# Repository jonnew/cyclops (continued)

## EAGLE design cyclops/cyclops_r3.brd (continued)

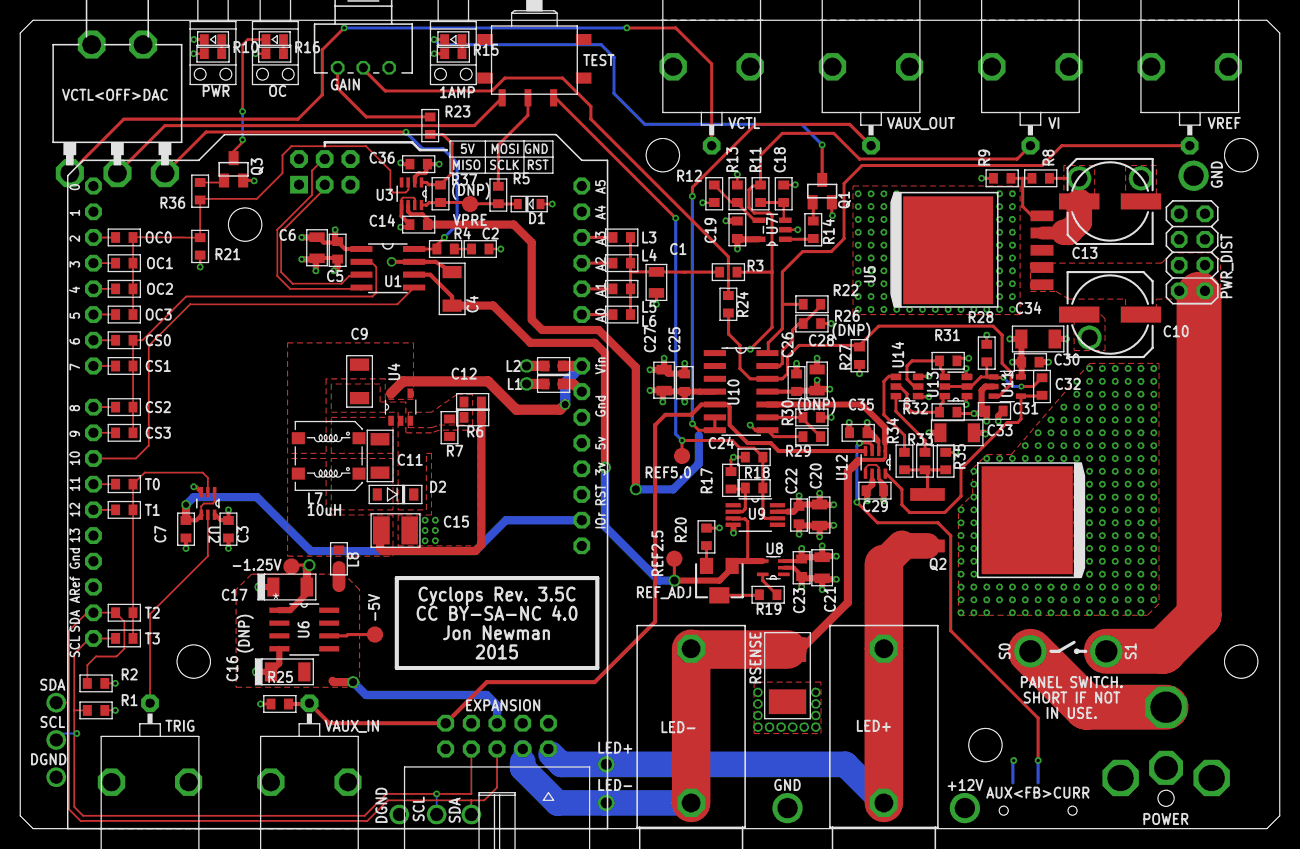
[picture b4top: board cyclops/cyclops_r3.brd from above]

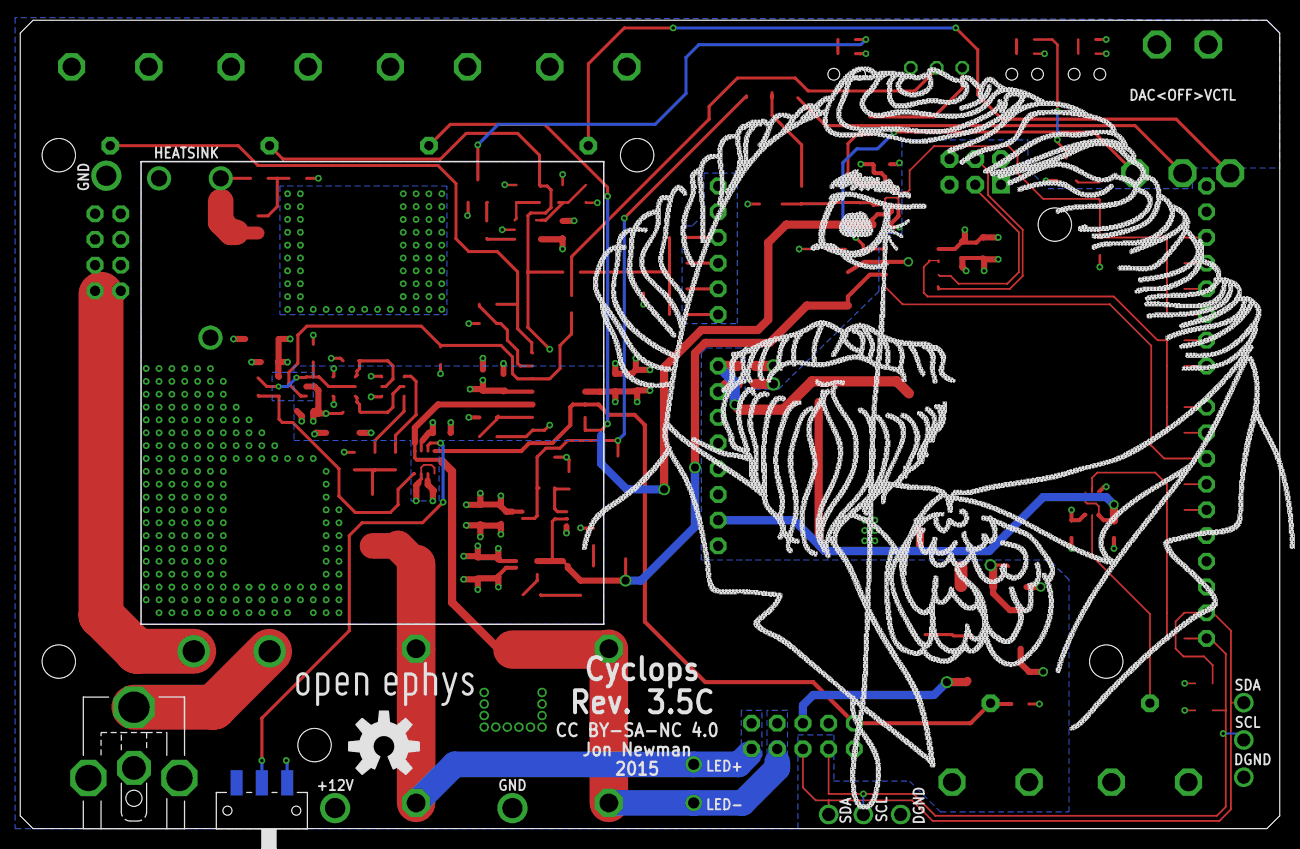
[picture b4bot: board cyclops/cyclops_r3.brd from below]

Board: 4 copper layers, 124.5 x 79.9 mm, 144 parts (6 on the bottom side), 80 nets.

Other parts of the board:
U$30: OPEN_EPHYS_LOGO
U$56: CYCLOPS_LOGO
U$60: OSHW-LOGO-L

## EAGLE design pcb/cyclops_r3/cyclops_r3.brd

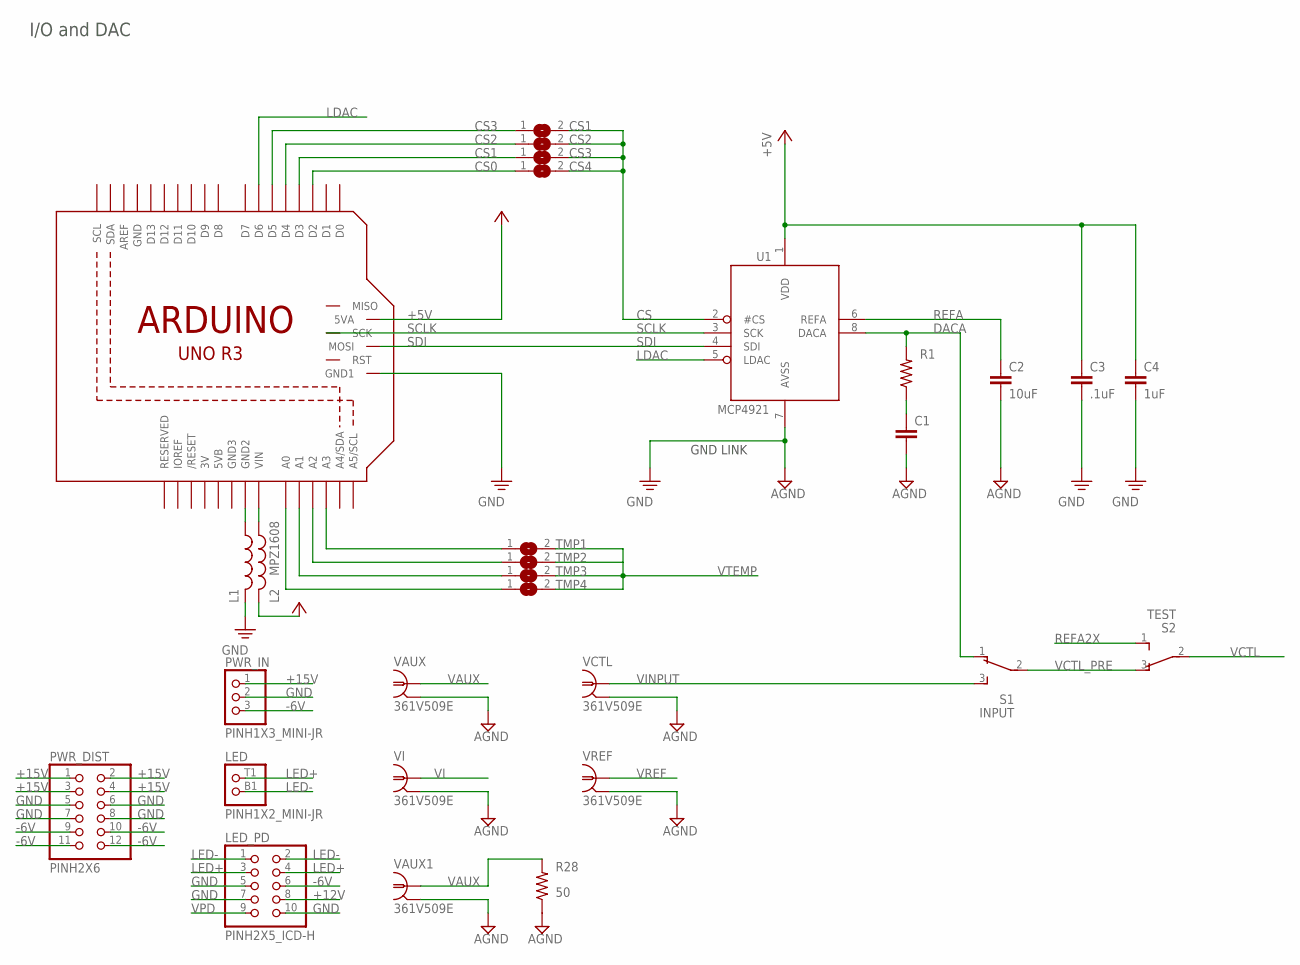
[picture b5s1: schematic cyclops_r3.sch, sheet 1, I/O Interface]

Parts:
ARDUNIO: ARDUINO_R3_ICSP_PINS; ARUDINOR3_PINS
C1: C_0603; 0603
C2: 10uF; 0805
C3: .1uF; 0603
C4: 1uF; 0805
CS1, CS2, CS3, CS4: SJ
L1, L2: MPZ1608; 0805
LED: PINH1X2_MINI-JR; MINI-JR-2X1
LED_PD: PINH2X5_ICD-H; 2X05-IDC
PWR_DIST: PINH2X6; 2X06-BIG
PWR_IN: PINH1X3_MINI-JR; MINI-JR-1X3
R1: R_0603; 0603
R28: 50; 0603
S1: INPUT; JS102011SAQN
S2: TEST; CFPA
TMP1, TMP2, TMP3, TMP4: SJ
U1: MCP4921; SO08
VAUX, VAUX1: 361V509E
VCTL: 361V509E
VI: 361V509E
VREF: 361V509E

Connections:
+5V: ARDUNIO.5VA, C3.1, C4.1, U1.1 (VDD)
+12V: L2.2, LED_PD.8; also elsewhere on the board
+15V: PWR_DIST.1, PWR_DIST.2, PWR_DIST.3, PWR_DIST.4, PWR_IN.1; also elsewhere on the board
-6V: LED_PD.6, PWR_DIST.9, PWR_DIST.10, PWR_DIST.11, PWR_DIST.12, PWR_IN.3; also elsewhere on the board
AGND: R28.1
CS: CS1.2, CS2.2, CS3.2, CS4.2, U1.2 (#CS)
CS0: ARDUNIO.D2, CS4.1
CS1: ARDUNIO.D3, CS3.1
CS2: ARDUNIO.D4, CS2.1
CS3: ARDUNIO.D5, CS1.1
CS4: ARDUNIO.A0, TMP4.1
CS5: ARDUNIO.A1, TMP3.1
CS6: ARDUNIO.A3, TMP1.1
CS8: ARDUNIO.A2, TMP2.1
DACA: R1.2, S1.1, U1.8 (DACA)
GND: ARDUNIO.GND1, C1.2, C2.2, C3.2, C4.2, L1.2, LED_PD.5, LED_PD.7, LED_PD.10, PWR_DIST.5, PWR_DIST.6, PWR_DIST.7, PWR_DIST.8, PWR_IN.2, U1.7 (AVSS), VAUX.2, VAUX.3 (2), VAUX1.2, VAUX1.3 (2), VCTL.2, VCTL.3 (2), VI.2, VI.3 (2), VREF.2, VREF.3 (2); also elsewhere on the board
LDAC: ARDUNIO.D6, U1.5 (LDAC)
LED+: LED.T1 (1), LED_PD.3, LED_PD.4; also elsewhere on the board
LED-: LED.B1 (2), LED_PD.1, LED_PD.2; also elsewhere on the board
unnamed: C1.1, R1.1
unnamed: ARDUNIO.GND2, L1.1
unnamed: ARDUNIO.VIN, L2.1
REFA: C2.1, U1.6 (REFA); also elsewhere on the board
REFA2X: S2.1 (3); also elsewhere on the board
SCLK: ARDUNIO.SCK, U1.3 (SCK)
SDI: ARDUNIO.MOSI, U1.4 (SDI)
VAUX: R28.2, VAUX.1, VAUX1.1; also elsewhere on the board
VCTL: S2.2; also elsewhere on the board
VCTL_PRE: S1.2, S2.3 (1)
VI: VI.1; also elsewhere on the board
VINPUT: S1.3, VCTL.1
VPD: LED_PD.9; also elsewhere on the board
VREF: VREF.1; also elsewhere on the board
VTEMP: TMP1.2, TMP2.2, TMP3.2, TMP4.2; also elsewhere on the board

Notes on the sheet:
GND LINK
I/O and DAC

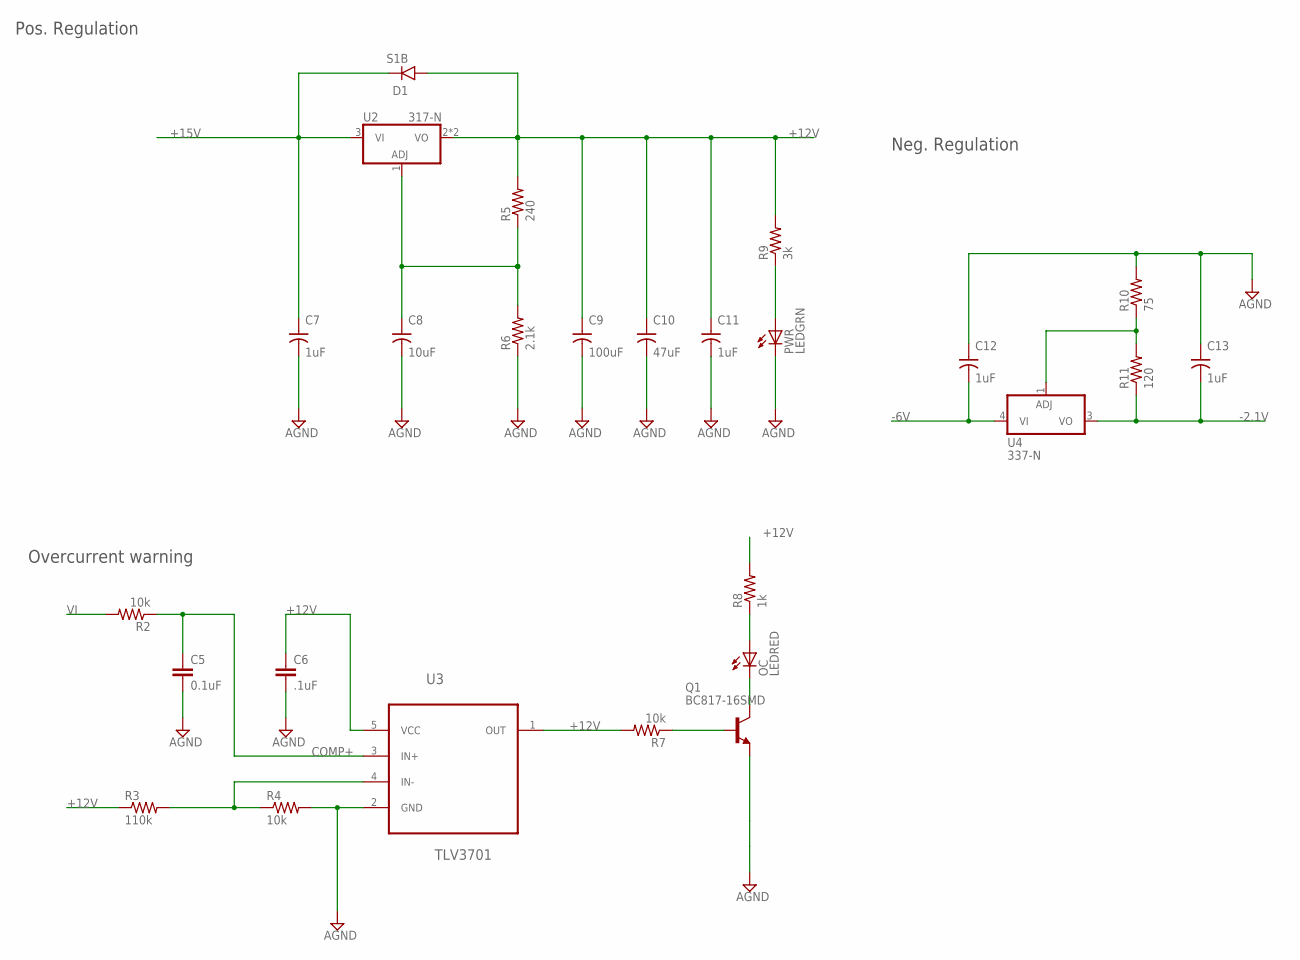
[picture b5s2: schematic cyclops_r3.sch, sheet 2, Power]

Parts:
C5: 0.1uF; 0603
C6: .1uF; 0603
C7, C11, C12, C13: 1uF; 1206-POL
C8: 10uF; 1206-POL
C9: 100uF; 153CLV-0807
C10: 47uF; 153CLV-0807
D1: S1B; SMA-DO214AC
OC: LEDRED; LED-0603
PWR: LEDGRN; LED-0603
Q1: BC817-16SMD; SOT23-BEC
R2, R4, R7: 10k; 0603
R3: 110k; 0603
R5: 240; 0603
R6: 2.1k; 0603
R8: 1k; 0603
R9: 3k; 0603
R10: 75; 0603
R11: 120; 0603
U2: 317-N; TO-263
U3: TLV3701; SOT95P280X145-5N
U4: 337-N; SOT223

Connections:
+12V: C6.1, C9.+, C10.+, C11.+, D1.A, R3.1, R5.2, R8.2, R9.2, U2.2 (VO), U2.4 (VO), U3.5 (VCC); also elsewhere on the board
+15V: C7.+, D1.C, U2.3 (VI); also elsewhere on the board
-2.1V: C13.-, R11.1, U4.3 (VO); also elsewhere on the board
-6V: C12.-, U4.4 (VI); also elsewhere on the board
COMP+: C5.1, R2.1, U3.3 (IN+)
GND: C5.2, C6.2, C7.-, C8.-, C9.-, C10.-, C11.-, C12.+, C13.+, PWR.C, Q1.E, R4.2, R6.1, R10.2, U3.2 (GND); also elsewhere on the board
unnamed: OC.A, R8.1
unnamed: PWR.A, R9.1
unnamed: R3.2, R4.1, U3.4 (IN-)
unnamed: OC.C, Q1.C
unnamed: R10.1, R11.2, U4.1 (ADJ)
unnamed: R7.2, U3.1 (OUT)
unnamed: Q1.B, R7.1
unnamed: C8.+, R5.1, R6.2, U2.1 (ADJ)
VI: R2.2; also elsewhere on the board

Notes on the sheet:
Pos. Regulation
Overcurrent warning
Neg. Regulation

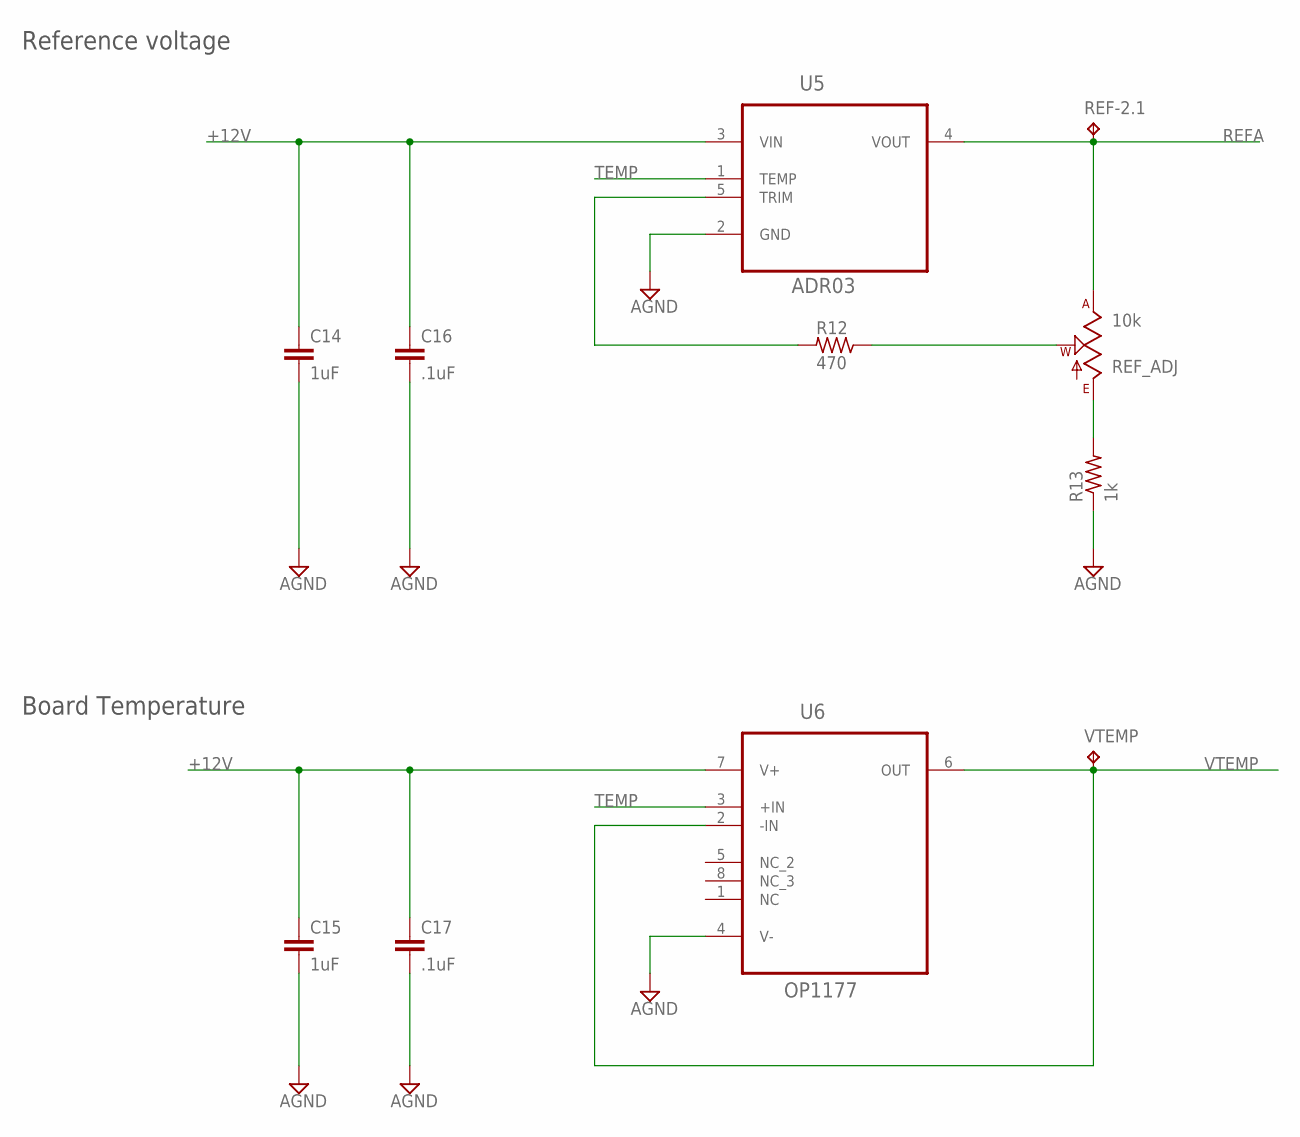
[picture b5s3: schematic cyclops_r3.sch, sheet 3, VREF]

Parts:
C14, C15: 1uF; 0805
C16, C17: .1uF; 0603
R12: 470; 0603
R13: 1k; 0603
REF-2.1: TPTP08R; TP08R
REF_ADJ: 10k; SM-42/43W
U5: ADR03; SOT65P210X110-5N
U6: OP1177; SOP65P490X110-8N
VTEMP: TPTP08R; TP08R

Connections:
+12V: C14.1, C15.1, C16.1, C17.1, U5.3 (VIN), U6.7 (V+); also elsewhere on the board
GND: C14.2, C15.2, C16.2, C17.2, R13.1, U5.2 (GND), U6.4 (V-); also elsewhere on the board
unnamed: R13.2, REF_ADJ.3 (E)
unnamed: R12.2, U5.5 (TRIM)
unnamed: R12.1, REF_ADJ.2 (W)
REFA: REF-2.1.TP, REF_ADJ.1 (A), U5.4 (VOUT); also elsewhere on the board
TEMP: U5.1 (TEMP), U6.3 (+IN)
VTEMP: U6.2 (-IN), U6.6 (OUT), VTEMP.TP; also elsewhere on the board

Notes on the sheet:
Reference voltage
Board Temperature

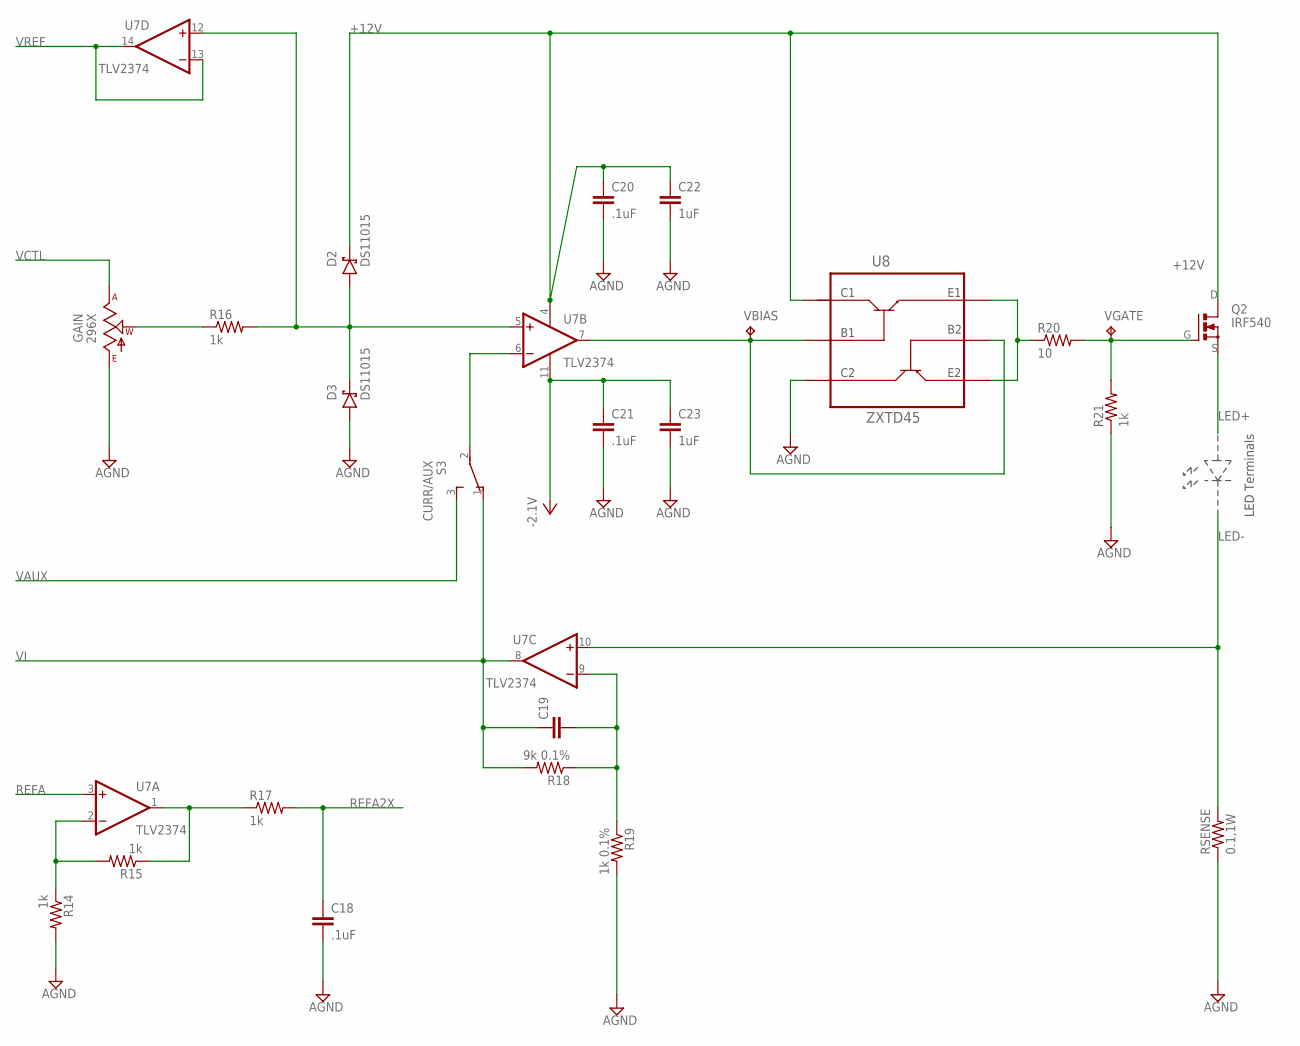
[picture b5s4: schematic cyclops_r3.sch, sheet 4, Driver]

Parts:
C18, C20, C21: .1uF; 0603
C19: C_0603; 0603
C22, C23: 1uF; 0805
D2, D3: DS11015; SOD123
GAIN: 296X; 296X-POT
Q2: IRF540; TO-262_01
R14, R15, R16, R17, R21: 1k; 0603
R18: 9k 0.1%; 0603
R19: 1k 0.1%; 0603
R20: 10; 0603
RSENSE: 0.1,1W; 2512W
S3: CURR/AUX; JS102011SAQN
U7: TLV2374; SO14
U8: ZXTD45; SOT23-6
VBIAS: TPTP08R; TP08R
VGATE: TPTP08R; TP08R

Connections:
+12V: C20.1, C22.1, D2.C, Q2.D, U7.4 (V+), U8.1 (C1); also elsewhere on the board
-2.1V: C21.1, C23.1, U7.11 (V-); also elsewhere on the board
GND: C18.2, C20.2, C21.2, C22.2, C23.2, D3.A, GAIN.E, R14.2, R19.2, R21.1, RSENSE.1, U8.3 (C2); also elsewhere on the board
LED+: Q2.S; also elsewhere on the board
LED-: RSENSE.2, U7.10 (+IN); also elsewhere on the board
unnamed: U7.7 (OUT), U8.2 (B1), U8.5 (B2), VBIAS.TP
unnamed: GAIN.W, R16.1
unnamed: R14.1, R15.2, U7.2 (-IN)
unnamed: R20.1, U8.4 (E2), U8.6 (E1)
unnamed: Q2.G, R20.2, R21.2, VGATE.TP
unnamed: C19.2, R18.1, R19.1, U7.9 (-IN)
REFA: U7.3 (+IN); also elsewhere on the board
REFA2X: C18.1, R17.2; also elsewhere on the board
VAUX: S3.3; also elsewhere on the board
VCTL: GAIN.A; also elsewhere on the board
VFB: S3.2, U7.6 (-IN)
VI: C19.1, R18.2, S3.1, U7.8 (OUT); also elsewhere on the board
VREF: U7.13 (-IN), U7.14 (OUT); also elsewhere on the board
VREFA2X: R15.1, R17.1, U7.1 (OUT)
_VREF: D2.A, D3.C, R16.2, U7.5 (+IN), U7.12 (+IN)

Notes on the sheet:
LED Terminals

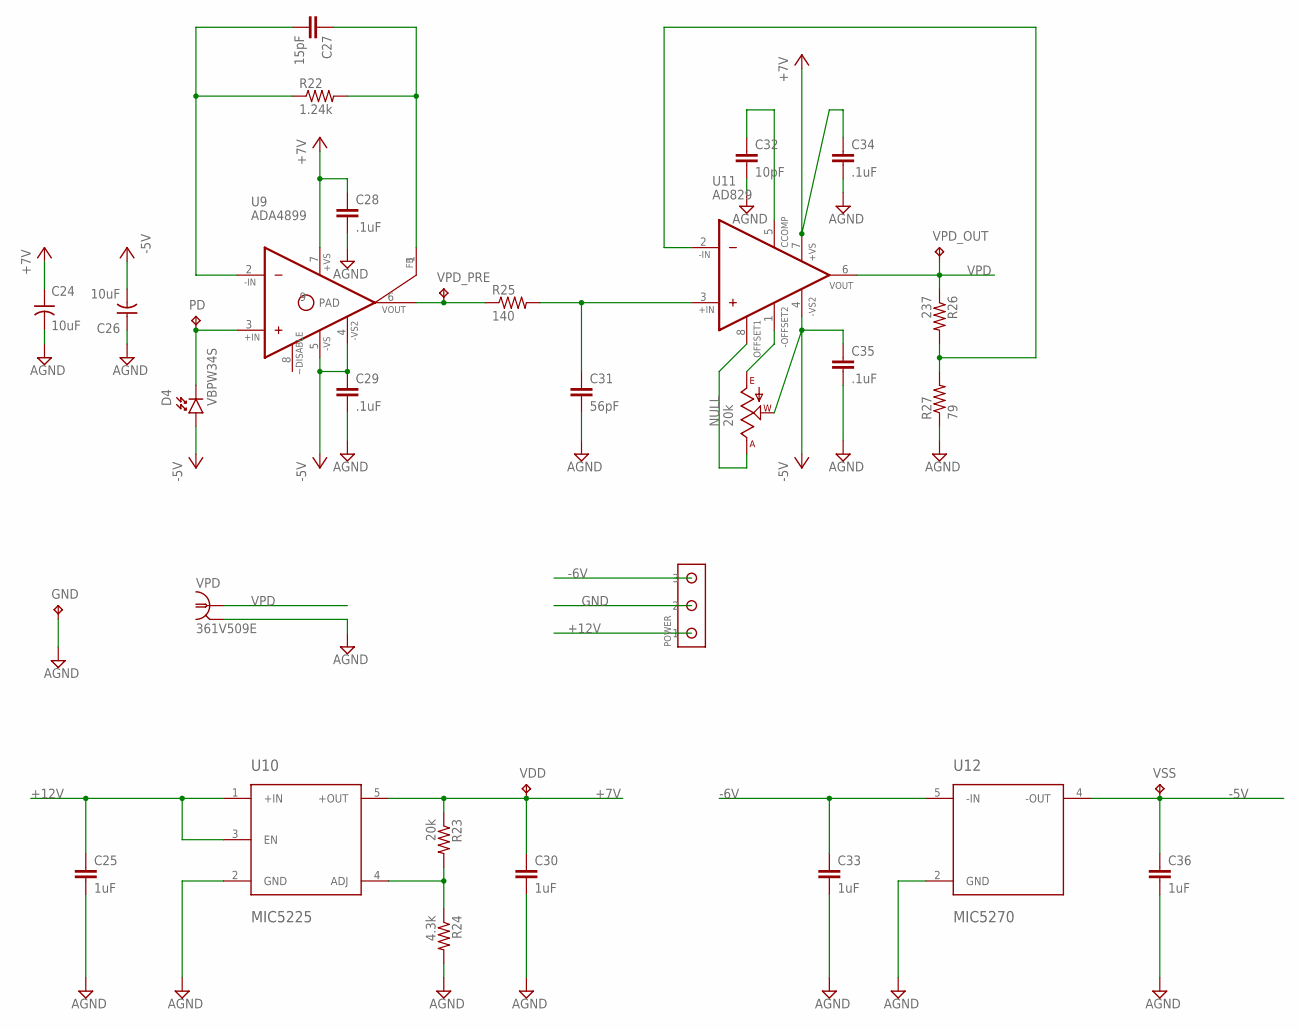
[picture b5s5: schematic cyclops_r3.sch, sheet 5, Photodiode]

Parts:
C24, C26: 10uF; 6032M-POL
C25, C30, C33, C36: 1uF; 0805
C27: 15pF; 0603
C28, C29, C34, C35: .1uF; 0603
C31: 56pF; 0603
C32: 10pF; 0603
D4: VBPW34S
GND: TPTP08R; TP08R
NULL: 20k; SM-42/43A
PD: TPTP08R; TP08R
POWER: S2B-PH-K-S; SCREW3
R22: 1.24k; 0603
R23: 20k; 0603
R24: 4.3k; 0603
R25: 140; 0603
R26: 237; 0603
R27: 79; 0603
U9: ADA4899; SOIC127P600X175-9N
U10: MIC5225; SOT65P210X110-5N
U11: AD829; SOIC127P600X175-8N
U12: MIC5270; SOT65P210X110-5N
VDD: TPTP08R; TP08R
VPD: 361V509E
VPD_OUT: TPTP08R; TP08R
VPD_PRE: TPTP08R; TP08R
VSS: TPTP08R; TP08R

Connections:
+7V: C24.+, C28.1, C30.1, C34.1, R23.1, U9.7 (+VS), U10.5 (+OUT), U11.7 (+VS), VDD.TP
+12V: C25.1, POWER.P$1 (1), U10.1 (+IN), U10.3 (EN); also elsewhere on the board
-5V: C26.-, C29.1, C35.1, C36.1, D4.A, NULL.2 (W), U9.4 (-VS_2), U9.5 (-VS), U11.4 (-VS), U12.4 (-OUT), VSS.TP
-6V: C33.1, POWER.P$3 (3), U12.5 (-IN); also elsewhere on the board
GND: C24.-, C25.2, C26.+, C28.2, C29.2, C30.2, C31.2, C32.2, C33.2, C34.2, C35.2, C36.2, GND.TP, POWER.P$2 (2), R24.2, R27.1, U10.2 (GND), U12.2 (GND), VPD.2, VPD.3 (2); also elsewhere on the board
unnamed: C27.1, R22.2, U9.1 (FEEDBACK)
unnamed: C27.2, R22.1, U9.2 (-IN)
unnamed: NULL.3 (E), U11.1 (OFS_2)
unnamed: D4.C, PD.TP, U9.3 (+IN)
unnamed: R25.1, U9.6 (VOUT), VPD_PRE.TP
unnamed: R23.2, R24.1, U10.4 (ADJ)
unnamed: R26.2, R27.2, U11.2 (-IN)
unnamed: NULL.1 (A), U11.8 (OFS)
unnamed: C32.1, U11.5 (CCOMP)
VPD: R26.1, U11.6 (OUTPUT), VPD.1, VPD_OUT.TP; also elsewhere on the board
VPD_PRE: C31.1, R25.2, U11.3 (+IN)

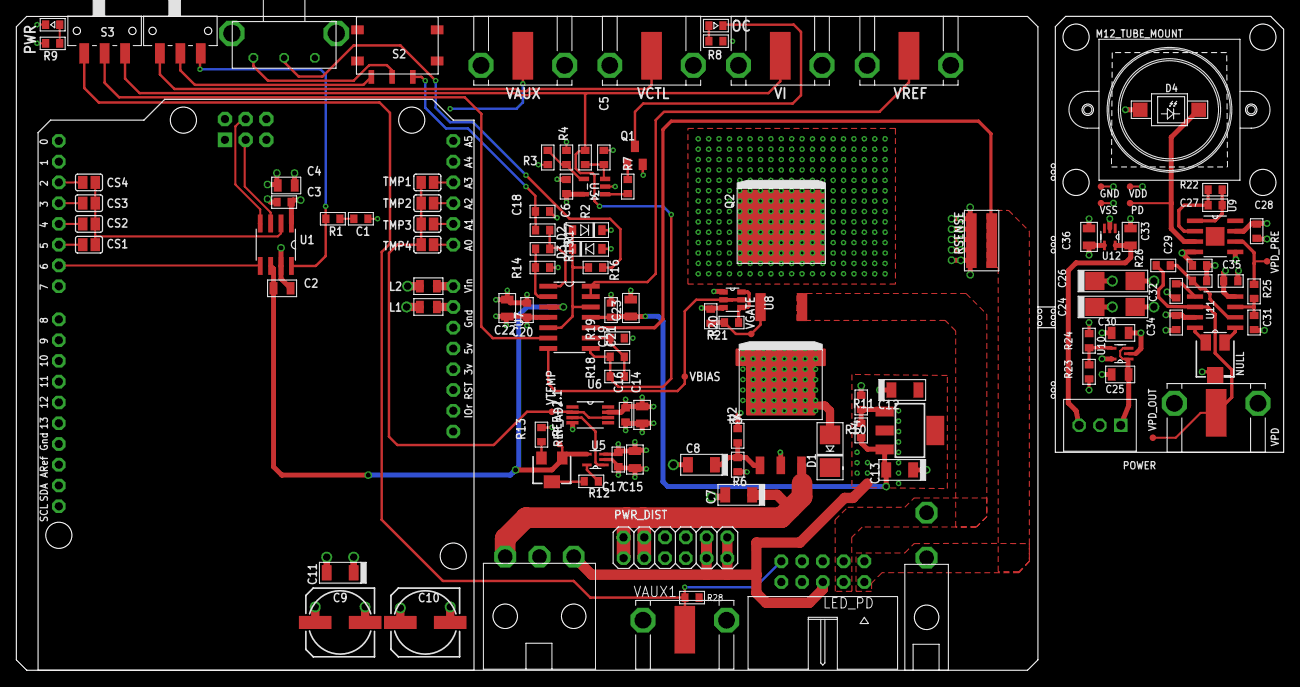
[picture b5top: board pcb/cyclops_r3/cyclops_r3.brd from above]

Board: 4 copper layers, 155.1 x 80.0 mm, 124 parts (0 on the bottom side), 68 nets.

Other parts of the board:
M12_TUBE_MOUNT: PT-LH001

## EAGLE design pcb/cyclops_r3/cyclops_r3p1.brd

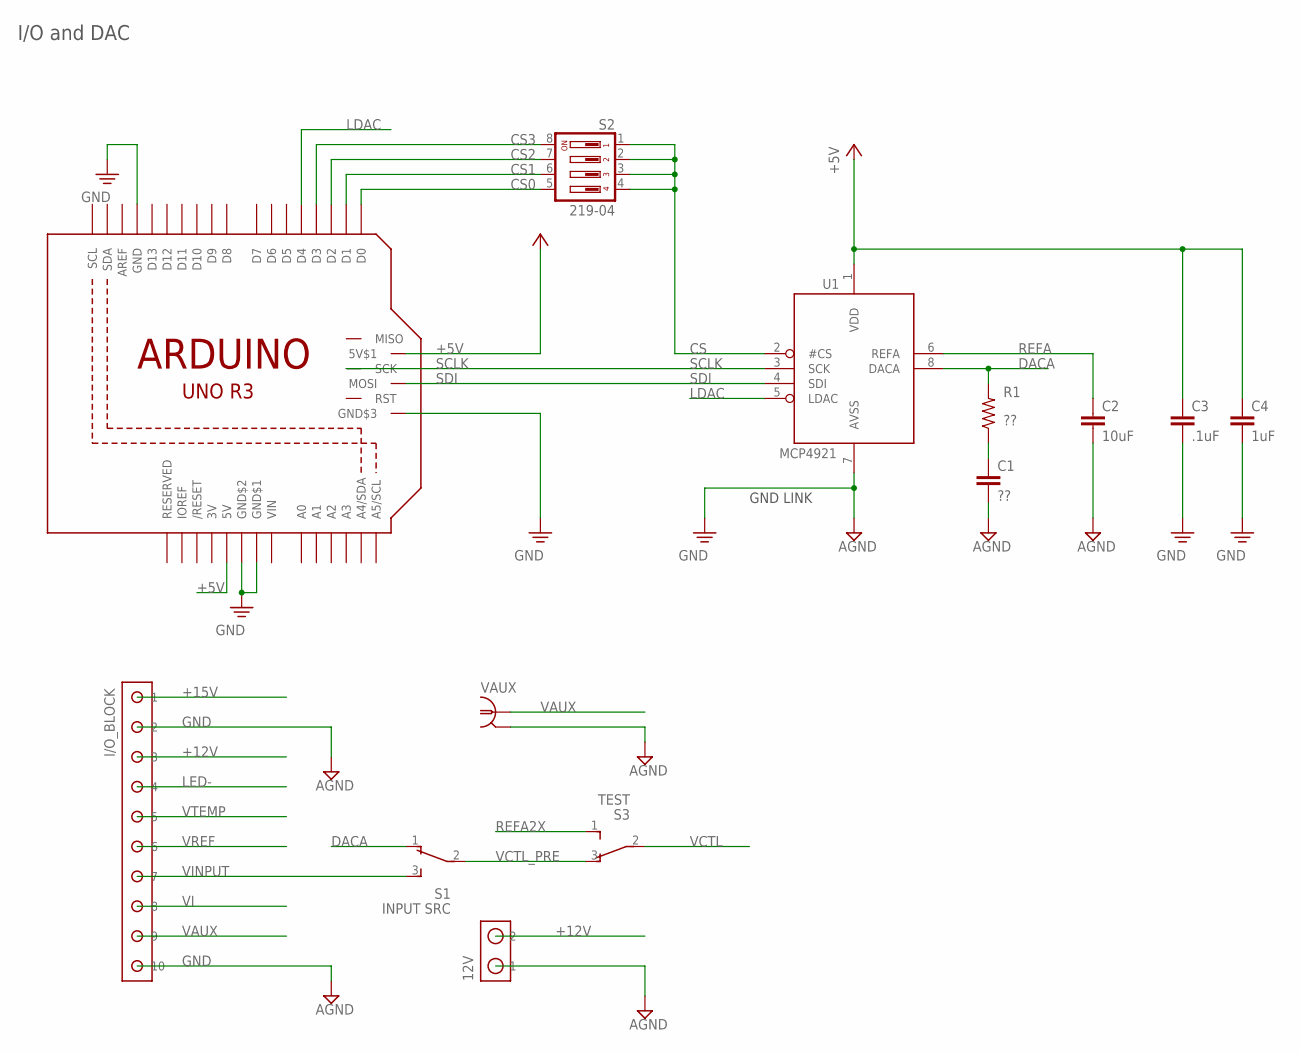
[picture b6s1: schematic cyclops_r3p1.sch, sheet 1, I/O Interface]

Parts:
12V: SCREW2
C1: ??; 0603
C2: 10uF; 0805
C3: .1uF; 0603
C4: 1uF; 0805
I/O_BLOCK: SCREW10_0.1-THRU; SCREW10
R1: ??; 0603
S1: INPUT SRC; PCM12
S2: 219-04; CTS-219-04
S3: TEST; CFPA
U1: MCP4921; SO08
U$1: ARDUINO_R3_ICSP; ARDUINOR3_ICSP
VAUX: BNC_V-BITE; 361V509E

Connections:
3V: U$1.3V
+5V: C3.1, C4.1, U1.1 (VDD), U$1.5V (5V$1), U$1.+5V (5V)
+12V: 12V.P$2 (2), I/O_BLOCK.P$3 (3); also elsewhere on the board
+15V: I/O_BLOCK.P$1 (1); also elsewhere on the board
CS: S2.1, S2.2, S2.3, S2.4, U1.2 (#CS)
CS0: S2.5, U$1.D0
CS1: S2.6, U$1.D1
CS2: S2.7, U$1.D2
CS3: S2.8, U$1.D3
DACA: R1.2, S1.1, U1.8 (DACA)
GND: 12V.P$1 (1), C1.2, C2.2, C3.2, C4.2, I/O_BLOCK.P$2 (2), I/O_BLOCK.P$10 (10), U1.7 (AVSS), U$1.GND, U$1.GND$1, U$1.GND$2, U$1.GND$3, VAUX.2, VAUX.3 (2); also elsewhere on the board
LDAC: U1.5 (LDAC), U$1.D4
LED-: I/O_BLOCK.P$4 (4); also elsewhere on the board
unnamed: C1.1, R1.1
REFA: C2.1, U1.6 (REFA); also elsewhere on the board
REFA2X: S3.1 (3); also elsewhere on the board
SCLK: U1.3 (SCK), U$1.SCK
SDI: U1.4 (SDI), U$1.MOSI
VAUX: I/O_BLOCK.P$9 (9), VAUX.1; also elsewhere on the board
VCTL: S3.2; also elsewhere on the board
VCTL_PRE: S1.2, S3.3 (1)
VI: I/O_BLOCK.P$8 (8); also elsewhere on the board
VIN: U$1.VIN
VINPUT: I/O_BLOCK.P$7 (7), S1.3
VREF: I/O_BLOCK.P$6 (6); also elsewhere on the board
VTEMP: I/O_BLOCK.P$5 (5); also elsewhere on the board

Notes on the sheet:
GND LINK
I/O and DAC

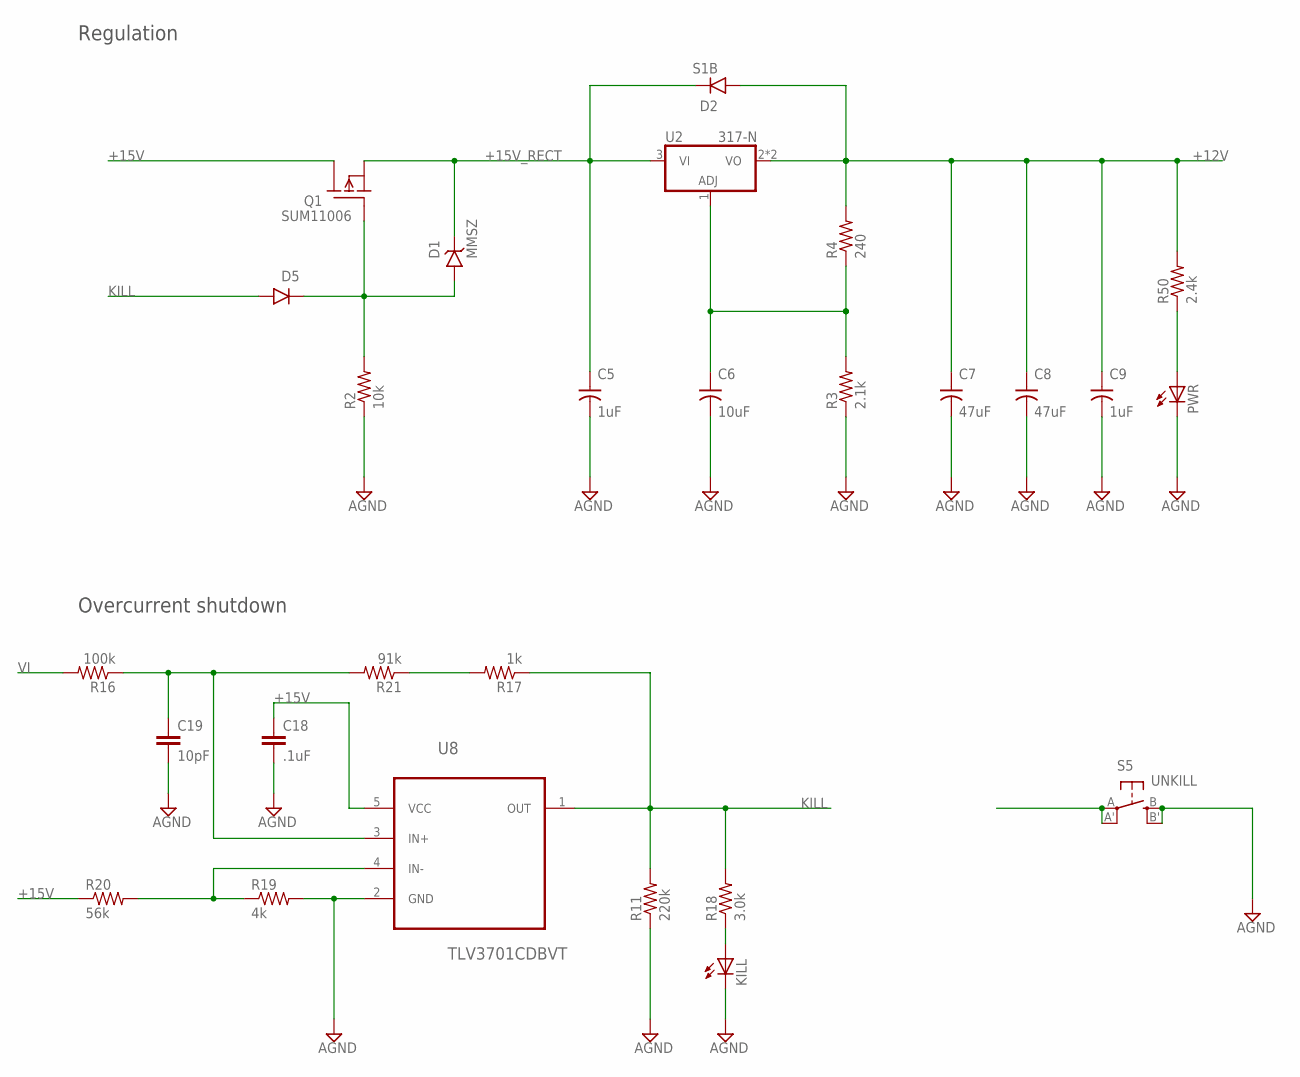
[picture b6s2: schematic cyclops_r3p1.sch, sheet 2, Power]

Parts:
C5, C9: 1uF; 1206-POL
C6: 10uF; 1206-POL
C7, C8: 47uF; 153CLV-0807
C18: .1uF; 0603
C19: 10pF; 0603
D1: MMSZ; SOD123
D2: S1B; SMA-DO214AC
D5: DIODESOD-323; SOD-323F
KILL: LEDYELLOW_0805; CHIP-LED0805
PWR: LEDYELLOW_0805; CHIP-LED0805
Q1: SUM11006; TO-262_01
R2: 10k; 0603
R3: 2.1k; 0603
R4: 240; 0603
R11: 220k; 0603
R16: 100k; 0603
R17: 1k; 0603
R18: 3.0k; 0603
R19: 4k; 0603
R20: 56k; 0603
R21: 91k; 0603
R50: 2.4k; 0603
S5: UNKILL; EVQ-Q2
U2: 317-N; TO-263
U8: TLV3701CDBVT; SOT95P280X145-5N

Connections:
+12V: C7.+, C8.+, C9.+, D2.A, R4.2, R50.2, U2.2 (VO), U2.4 (VO); also elsewhere on the board
+15V: C18.1, Q1.D, R20.1, U8.5 (VCC); also elsewhere on the board
+15V_RECT: C5.+, D1.C, D2.C, Q1.S, U2.3 (VI)
COMP+: C19.1, R16.1, R21.2, S5.A, S5.A' (P1), U8.3 (IN+)
GND: C5.-, C6.-, C7.-, C8.-, C9.-, C18.2, C19.2, KILL.C, PWR.C, R2.1, R3.1, R11.1, R19.2, S5.B (S), S5.B' (S1), U8.2 (GND); also elsewhere on the board
KILL: D5.A, R11.2, R17.1, R18.2, U8.1 (OUT)
unnamed: PWR.A, R50.1
unnamed: R19.1, R20.2, U8.4 (IN-)
unnamed: R17.2, R21.1
unnamed: KILL.A, R18.1
unnamed: D1.A, D5.C, Q1.G, R2.2
unnamed: C6.+, R3.2, R4.1, U2.1 (ADJ)
VI: R16.2; also elsewhere on the board

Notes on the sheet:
Regulation
Overcurrent shutdown

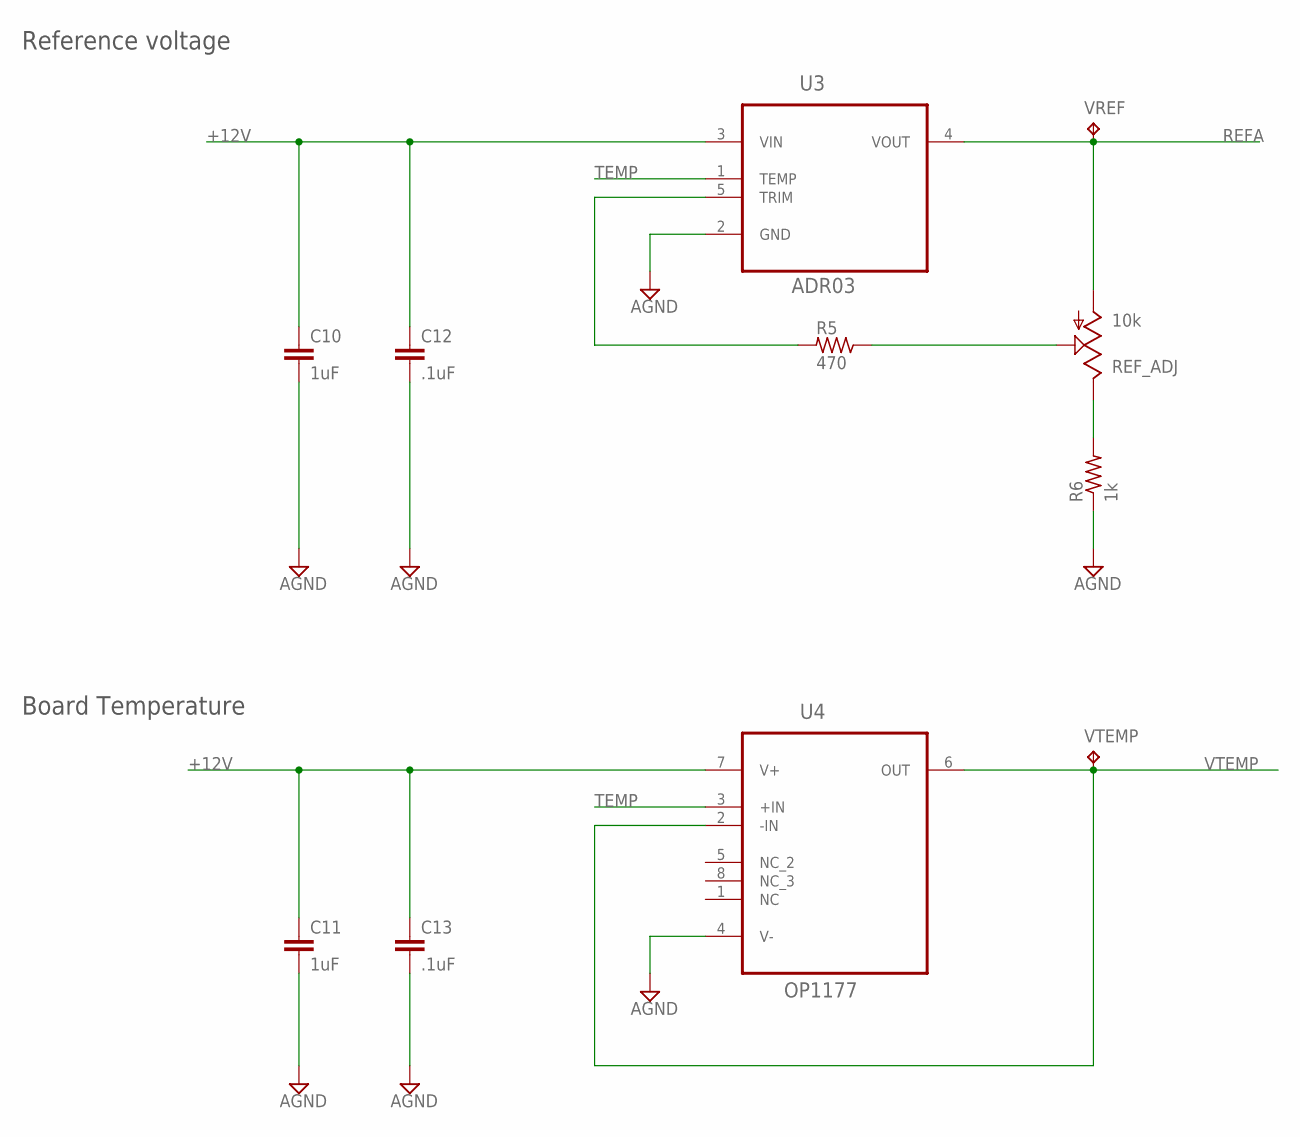
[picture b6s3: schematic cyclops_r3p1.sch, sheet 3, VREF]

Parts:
C10, C11: 1uF; 0805
C12, C13: .1uF; 0603
R5: 470; 0603
R6: 1k; 0603
REF_ADJ: 10k; SM-42/43W
U3: ADR03; SOT65P210X110-5N
U4: OP1177; SOP65P490X110-8N
VREF: TPTP08R; TP08R
VTEMP: TPTP08R; TP08R

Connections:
+12V: C10.1, C11.1, C12.1, C13.1, U3.3 (VIN), U4.7 (V+); also elsewhere on the board
GND: C10.2, C11.2, C12.2, C13.2, R6.1, U3.2 (GND), U4.4 (V-); also elsewhere on the board
unnamed: R6.2, REF_ADJ.3 (E)
unnamed: R5.2, U3.5 (TRIM)
unnamed: R5.1, REF_ADJ.2 (S)
REFA: REF_ADJ.1 (A), U3.4 (VOUT), VREF.TP; also elsewhere on the board
TEMP: U3.1 (TEMP), U4.3 (+IN)
VTEMP: U4.2 (-IN), U4.6 (OUT), VTEMP.TP; also elsewhere on the board

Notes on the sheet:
Reference voltage
Board Temperature

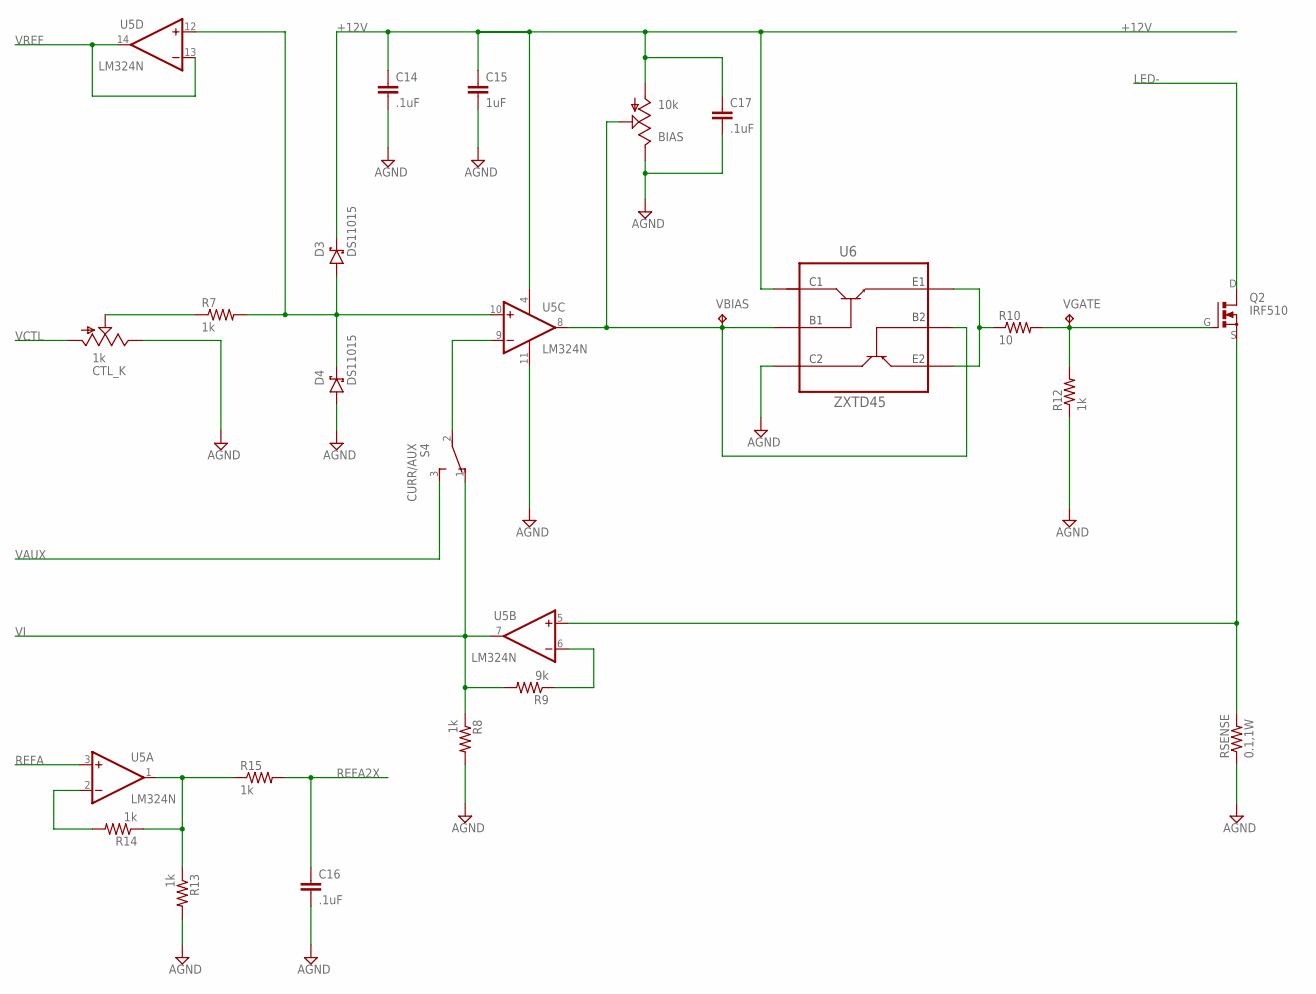
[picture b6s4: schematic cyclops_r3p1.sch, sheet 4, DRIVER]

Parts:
BIAS: 10k; SM-42/43W
C14, C16, C17: .1uF; 0603
C15: 1uF; 0805
CTL_K: 1k; SM-42/43A
D3, D4: DS11015; SOD123
Q2: IRF510; TO-262_01
R7, R8, R12, R13, R14, R15: 1k; 0603
R9: 9k; 0603
R10: 10; 0603
RSENSE: 0.1,1W; 2512
S4: CURR/AUX; PCM12
U5: LM324N; SO14
U6: ZXTD45; SOT23-6
VBIAS: TPTP08R; TP08R
VGATE: TPTP08R; TP08R

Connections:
+12V: BIAS.1 (A), C14.1, C15.1, C17.1, D3.C, U5.4 (V+), U6.1 (C1); also elsewhere on the board
GND: BIAS.3 (E), C14.2, C15.2, C16.2, C17.2, CTL_K.3 (E), D4.A, R8.2, R12.1, R13.2, RSENSE.1, U5.11 (V-), U6.3 (C2); also elsewhere on the board
LED-: Q2.D; also elsewhere on the board
unnamed: Q2.S, RSENSE.2, U5.5 (+IN)
unnamed: BIAS.2 (S), U5.8 (OUT), U6.2 (B1), U6.5 (B2), VBIAS.TP
unnamed: CTL_K.2 (S), R7.1
unnamed: R14.2, U5.2 (-IN)
unnamed: R10.1, U6.4 (E2), U6.6 (E1)
unnamed: Q2.G, R10.2, R12.2, VGATE.TP
unnamed: R9.1, U5.6 (-IN)
REFA: U5.3 (+IN); also elsewhere on the board
REFA2X: C16.1, R15.2; also elsewhere on the board
VAUX: S4.3; also elsewhere on the board
VCTL: CTL_K.1 (A); also elsewhere on the board
VFB: S4.2, U5.9 (-IN)
VI: R8.1, R9.2, S4.1, U5.7 (OUT); also elsewhere on the board
VREF: U5.13 (-IN), U5.14 (OUT); also elsewhere on the board
VREFA2X: R13.1, R14.1, R15.1, U5.1 (OUT)
_VREF: D3.A, D4.C, R7.2, U5.10 (+IN), U5.12 (+IN)
